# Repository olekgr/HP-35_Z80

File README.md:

# HP-35-Z80
Build HP35 scientic calculator clone with Z80 cpu from scratch.

## Intro

This DIY page is about building a HP35 clone. But without using emulators, HP microcode etc. I have always wanted to write original algorithms, created by David S. Cochran and provided by William E. Egbert in 4 editions of 1977's HP Journal, please see <a href="https://github.com/olekgr/HP-35_Z80/tree/main/arch">arch</a>.

As the original HP35 was built 50 years ago, this is a good time to do the same.

All fuctions are written with BCD arithmetic, I haven't used BCD - to binary conversion.

## Number format

For this HP35 clone, I chose a BCD floating point format. It uses an exponent byte, a sign byte and eight bytes of fractional part  (80 bits total). 

The sign byte holds 0x00 for positive numbers and 0x09 for negative, this byte also can hold other values in case of positive or negative overflow.

The exponent byte is the signed number power of 10, plus the offset 0x80. Note that exponent is not in BCD form, but binary. This greatly simplifies addition and substraction algorithms. Range is limited to 10^-99 and 10^99.

The fractional part is represented as 16 BCD digits packed two per byte, with an implied decimal point after the first digit (normalized form).

Only the first 12 digits are always displayed to the user; the last 4 digits exists to maintain precision (guard digits). All internal calculations are done with 16 digits, next the displayed result is always rounded to 12 digits.

As an examples:

1 is stored as 80_00_10_00_00_00_00_00_00_00

0.1 is stored as 7f_00_10_00_00_00_00_00_00_00

123 is stored as 82_00_12_30_00_00_00_00_00_00

pi/4 is stored  as 7f_00_78_53_98_16_33_97_44_83

## Negative numbers

Negative numbers are always stored as their 10's complement, with 0x09 at sign position. For example:

-1 is stored as 80_09_90_00_00_00_00_00_00_00

-12 is stored as 81_09_88_00_00_00_00_00_00_00

## Why Z80?

The Z80 is only four years younger than the HP35 :)

It has few instructions useful for making BCD arithmetic:

* RLD - rotate left decimal (used for shifting BCD numbers to the left)

* RRD - rotate right decimal (used for shifting BCD numbers to the right)

* DAA - decimal accumulator adjust (addition and substraction of BCD numbers)

## Speed

Calculations are fast, much faster than original HP35, we get the result immediately after pressing the key.

## Operating

I have made every effort to make this calculator work exactly like the original. Some functions were simple, others (most notably the CHS key which changes the sign of a number before or after it was entered) difficult. Either way, the calculator executes all the examples in the HP35 manual the same way. I have to say I use this calculator every day and it does a great job.

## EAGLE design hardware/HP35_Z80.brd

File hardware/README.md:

# HP-35-Z80
EAGLE PCB source files, schematic, gerbers etc.

## Hardware
The hardware is made as simple as possible. It consists of a Z80 CPU, 8K RAM, 8K ROM, input and output buffers and a simple address decoder. The main program takes about 6K, so it fits easily in 8K EEPROM. I chose 8K RAM (6264) only and because of availability, not need, I think 1-2K would be enough for stack and variables.

## Memory map
0000h-2000h ROM

8000h-A000h RAM

## BOM
* IC1 - Z80 - main CPU
* IC2 - AT28C64 - ROM
* IC3 - 6264 - RAM
* IC4 - 74HCT32 - control signals (memory read, write)
* IC5 - 74HCT154 - display multiplexer
* IC6 - 74HCT138 - address decoder (only 3 periph used)
* IC7 - 74HCT541 - keyboard input
* IC8, IC9 - 74HCT574 - digit and position for multiplexing 7-seg display
* OSC - 8MHz DIL14 - main clock

All SMT components in 1206 case (except C11 - "D" case)
* C1 - 10u 
* R1..R9 - 10k 
* C2..C10 100n
* R10..R17 - 220R (HP used inductors here for power saving :)
* DIS1..4 - common cathode 4x7 segment display (eg. SH5461AS)
* X1,X2 - USB MINI sockets (+5V power supply, for convenience left and right side)
* keys 1..35 Cherry MX switches

## Errors

None found :)

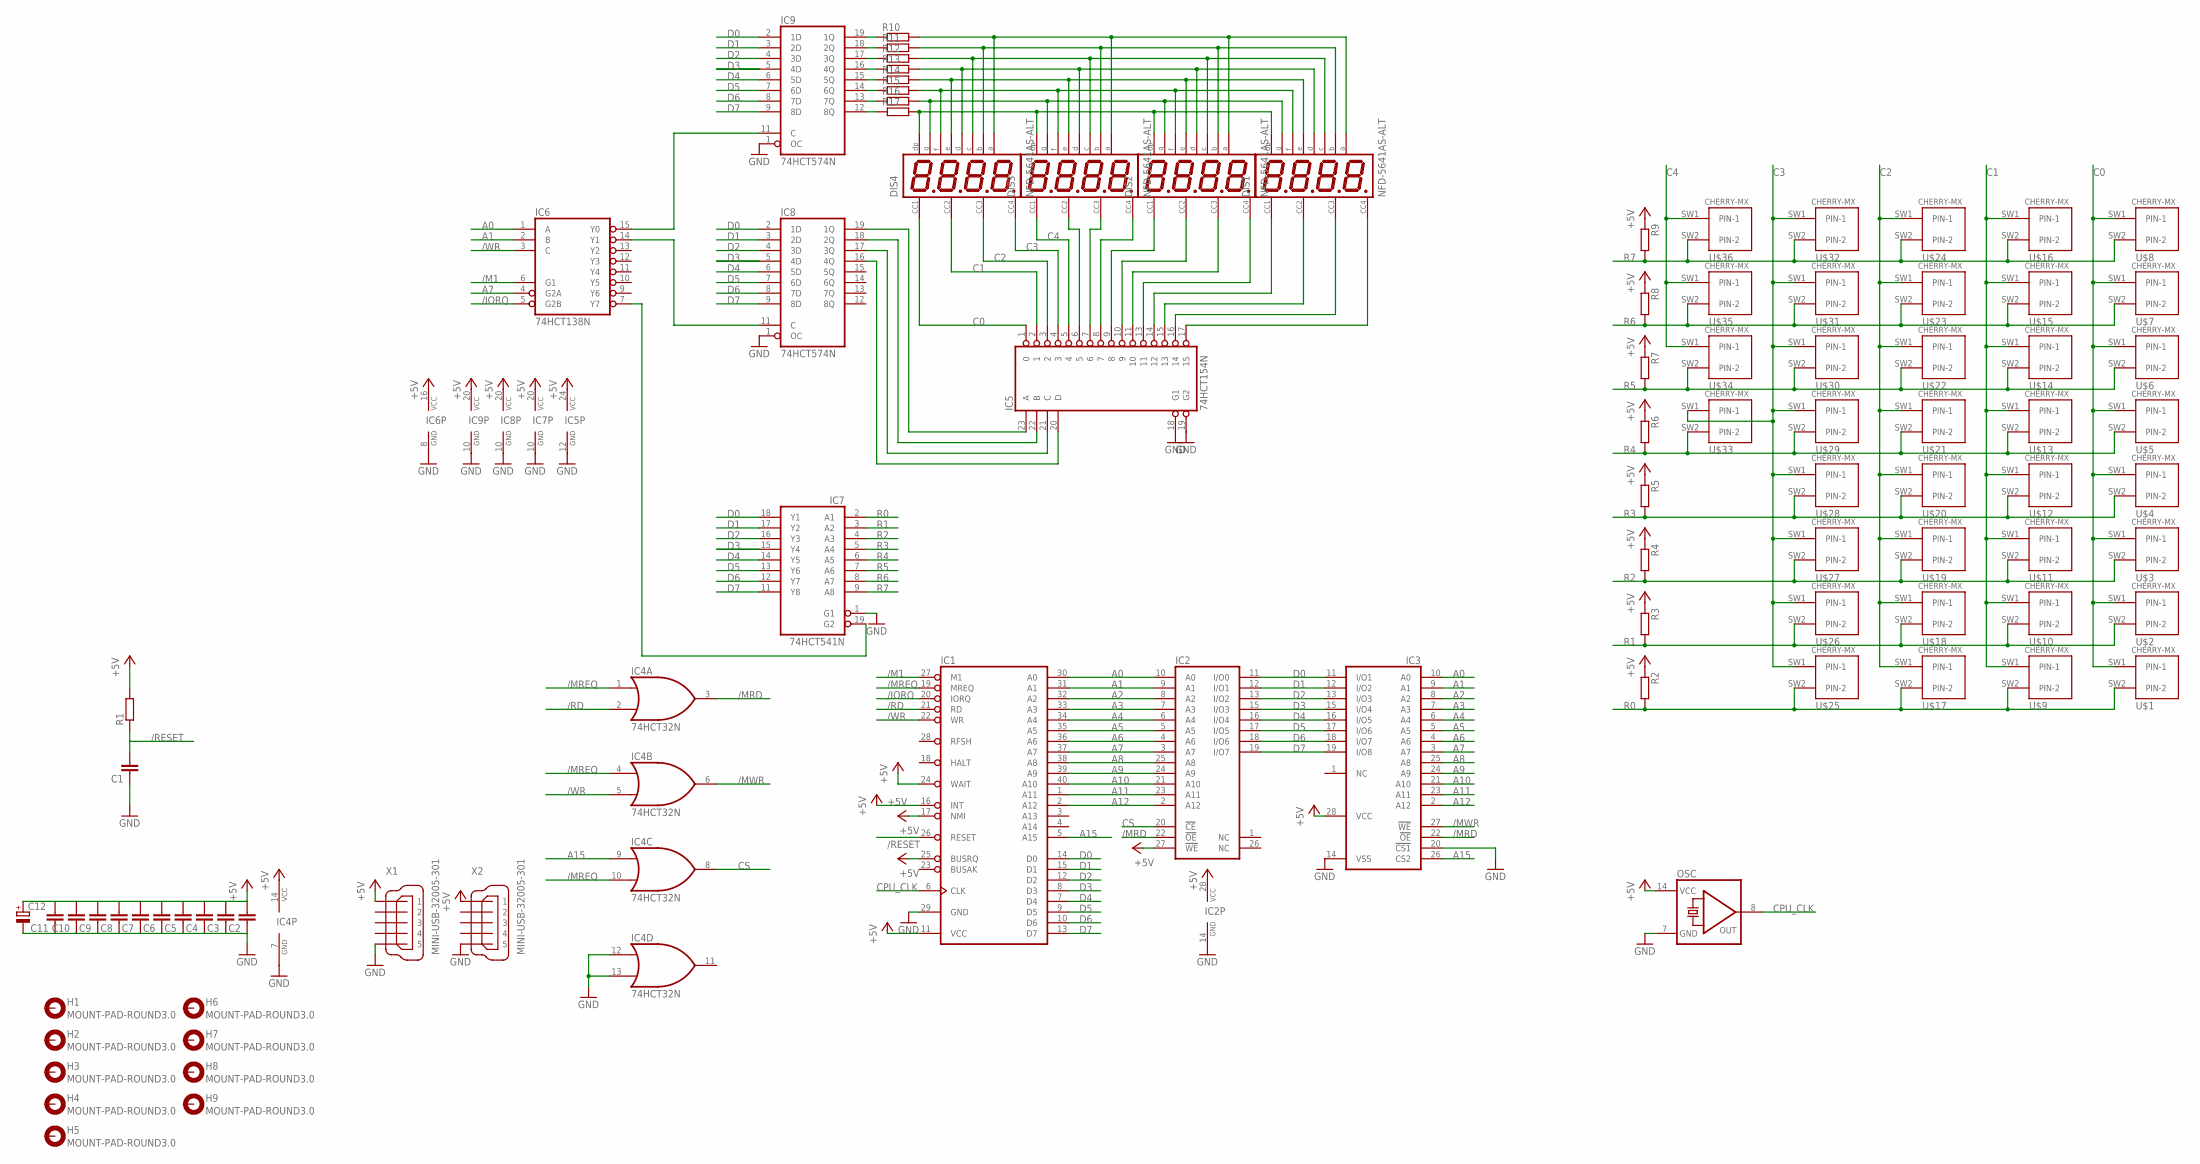
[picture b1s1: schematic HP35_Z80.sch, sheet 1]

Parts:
C1, C2, C3, C4, C5, C6, C7, C8, C9, C10, C11: C-EUC1206; C1206
C12: CPOL-EUSMCD; SMC_D
DIS1, DIS2, DIS3, DIS4: NFD-5641AS-ALT; NFD-5641
H1, H2, H3, H4, H5, H6, H7, H8, H9: MOUNT-PAD-ROUND3.0; 3,0-PAD
IC1: Z80CPU; DIL40
IC2: 78C64P; DIL28-6
IC3: 6264A; DIL28-6
IC4: 74HCT32N; DIL14
IC5: 74HCT154N; DIL24-6
IC6: 74HCT138N; DIL16
IC7: 74HCT541N; DIL20
IC8, IC9: 74HCT574N; DIL20
OSC: QG5860; DIL14S
R1, R2, R3, R4, R5, R6, R7, R8, R9, R10, R11, R12, R13, R14, R15, R16, R17: R-EU_R1206; R1206
U$1, U$2, U$3, U$4, U$5, U$6, U$7, U$8, U$9, U$10, U$11, U$12, U$13, U$14, U$15, U$16, U$17, U$18, U$19, U$20, U$21, U$22, U$23, U$24, U$25, U$26, U$27, U$28, U$29, U$30, U$31, U$32, U$33, U$34, U$35, U$36: CHERRY-MX
X1, X2: MINI-USB-32005-301; 32005-301

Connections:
+5V: C2.2, C3.2, C4.2, C5.2, C6.2, C7.2, C8.2, C9.2, C10.2, C11.2, C12.+, IC1.11 (VCC), IC1.16 (INT), IC1.17 (NMI), IC1.24 (WAIT), IC1.25 (BUSRQ), IC2.27 (!WE), IC2.28 (VCC), IC3.28 (VCC), IC4.14 (VCC), IC5.24 (VCC), IC6.16 (VCC), IC7.20 (VCC), IC8.20 (VCC), IC9.20 (VCC), OSC.14 (VCC), R1.2, R2.1, R3.1, R4.1, R5.1, R6.1, R7.1, R8.1, R9.1, X1.1, X2.1
/IORQ: IC1.20 (IORQ), IC6.5 (G2B)
/M1: IC1.27 (M1), IC6.6 (G1)
/MRD: IC2.22 (!OE), IC3.22 (!OE), IC4.3 (O)
/MREQ: IC1.19 (MREQ), IC4.1 (I0), IC4.4 (I0), IC4.10 (I1)
/MWR: IC3.27 (!WE), IC4.6 (O)
/RD: IC1.21 (RD), IC4.2 (I1)
/RESET: C1.2, IC1.26 (RESET), R1.1
/WR: IC1.22 (WR), IC4.5 (I1), IC6.3 (C)
A0: IC1.30 (A0), IC2.10 (A0), IC3.10 (A0), IC6.1 (A)
A1: IC1.31 (A1), IC2.9 (A1), IC3.9 (A1), IC6.2 (B)
A2: IC1.32 (A2), IC2.8 (A2), IC3.8 (A2)
A3: IC1.33 (A3), IC2.7 (A3), IC3.7 (A3)
A4: IC1.34 (A4), IC2.6 (A4), IC3.6 (A4)
A5: IC1.35 (A5), IC2.5 (A5), IC3.5 (A5)
A6: IC1.36 (A6), IC2.4 (A6), IC3.4 (A6)
A7: IC1.37 (A7), IC2.3 (A7), IC3.3 (A7), IC6.4 (G2A)
A8: IC1.38 (A8), IC2.25 (A8), IC3.25 (A8)
A9: IC1.39 (A9), IC2.24 (A9), IC3.24 (A9)
A10: IC1.40 (A10), IC2.21 (A10), IC3.21 (A10)
A11: IC1.1 (A11), IC2.23 (A11), IC3.23 (A11)
A12: IC1.2 (A12), IC2.2 (A12), IC3.2 (A12)
A15: IC1.5 (A15), IC3.26 (CS2), IC4.9 (I0)
C0: DIS4.P$12, IC5.1 (0), U$1.SW1 (PIN-1), U$2.SW1 (PIN-1), U$3.SW1 (PIN-1), U$4.SW1 (PIN-1), U$5.SW1 (PIN-1), U$6.SW1 (PIN-1), U$7.SW1 (PIN-1), U$8.SW1 (PIN-1)
C1: DIS4.P$9, IC5.2 (1), U$9.SW1 (PIN-1), U$10.SW1 (PIN-1), U$11.SW1 (PIN-1), U$12.SW1 (PIN-1), U$13.SW1 (PIN-1), U$14.SW1 (PIN-1), U$15.SW1 (PIN-1), U$16.SW1 (PIN-1)
C2: DIS4.P$8, IC5.3 (2), U$17.SW1 (PIN-1), U$18.SW1 (PIN-1), U$19.SW1 (PIN-1), U$20.SW1 (PIN-1), U$21.SW1 (PIN-1), U$22.SW1 (PIN-1), U$23.SW1 (PIN-1), U$24.SW1 (PIN-1)
C3: DIS4.P$6, IC5.4 (3), U$25.SW1 (PIN-1), U$26.SW1 (PIN-1), U$27.SW1 (PIN-1), U$28.SW1 (PIN-1), U$29.SW1 (PIN-1), U$30.SW1 (PIN-1), U$31.SW1 (PIN-1), U$32.SW1 (PIN-1), U$33.SW1 (PIN-1)
C4: DIS3.P$12, IC5.5 (4), U$34.SW1 (PIN-1), U$35.SW1 (PIN-1), U$36.SW1 (PIN-1)
CPU_CLK: IC1.6 (CLK), OSC.8 (OUT)
CS: IC2.20 (!CE), IC4.8 (O)
D0: IC1.14 (D0), IC2.11 (I/O0), IC3.11 (I/O1), IC7.18 (Y1), IC8.2 (1D), IC9.2 (1D)
D1: IC1.15 (D1), IC2.12 (I/O1), IC3.12 (I/O2), IC7.17 (Y2), IC8.3 (2D), IC9.3 (2D)
D2: IC1.12 (D2), IC2.13 (I/O2), IC3.13 (I/O3), IC7.16 (Y3), IC8.4 (3D), IC9.4 (3D)
D3: IC1.8 (D3), IC2.15 (I/O3), IC3.15 (I/O4), IC7.15 (Y4), IC8.5 (4D), IC9.5 (4D)
D4: IC1.7 (D4), IC2.16 (I/O4), IC3.16 (I/O5), IC7.14 (Y5), IC8.6 (5D), IC9.6 (5D)
D5: IC1.9 (D5), IC2.17 (I/O5), IC3.17 (I/O6), IC7.13 (Y6), IC8.7 (6D), IC9.7 (6D)
D6: IC1.10 (D6), IC2.18 (I/O6), IC3.18 (I/O7), IC7.12 (Y7), IC8.8 (7D), IC9.8 (7D)
D7: IC1.13 (D7), IC2.19 (I/O7), IC3.19 (I/O8), IC7.11 (Y8), IC8.9 (8D), IC9.9 (8D)
GND: C1.1, C2.1, C3.1, C4.1, C5.1, C6.1, C7.1, C8.1, C9.1, C10.1, C11.1, C12.-, IC1.29 (GND), IC2.14 (GND), IC3.14 (VSS), IC3.20 (!CS1), IC4.7 (GND), IC4.12 (I0), IC4.13 (I1), IC5.12 (GND), IC5.18 (G1), IC5.19 (G2), IC6.8 (GND), IC7.1 (G1), IC7.10 (GND), IC8.1 (OC), IC8.10 (GND), IC9.1 (OC), IC9.10 (GND), OSC.7 (GND), X1.5, X2.5
unnamed: IC6.15 (Y0), IC9.11 (C)
unnamed: IC5.20 (D), IC8.16 (4Q)
unnamed: IC6.14 (Y1), IC8.11 (C)
unnamed: IC5.21 (C), IC8.17 (3Q)
unnamed: IC5.22 (B), IC8.18 (2Q)
unnamed: IC5.23 (A), IC8.19 (1Q)
unnamed: IC6.7 (Y7), IC7.19 (G2)
unnamed: IC9.12 (8Q), R17.1
unnamed: IC9.13 (7Q), R16.1
unnamed: IC9.14 (6Q), R15.1
unnamed: IC9.15 (5Q), R14.1
unnamed: DIS3.P$9, IC5.6 (5)
unnamed: DIS3.P$8, IC5.7 (6)
unnamed: DIS3.P$6, IC5.8 (7)
unnamed: DIS2.P$12, IC5.9 (8)
unnamed: DIS2.P$9, IC5.10 (9)
unnamed: DIS2.P$8, IC5.11 (10)
unnamed: DIS2.P$6, IC5.13 (11)
unnamed: DIS1.P$12, IC5.14 (12)
unnamed: DIS1.P$9, IC5.15 (13)
unnamed: DIS1.P$8, IC5.16 (14)
unnamed: DIS1.P$6, IC5.17 (15)
unnamed: IC9.16 (4Q), R13.1
unnamed: IC9.17 (3Q), R12.1
unnamed: IC9.18 (2Q), R11.1
unnamed: IC9.19 (1Q), R10.1
unnamed: DIS1.P$11, DIS2.P$11, DIS3.P$11, DIS4.P$11, R10.2
unnamed: DIS1.P$3, DIS2.P$3, DIS3.P$3, DIS4.P$3, R17.2
unnamed: DIS1.P$5, DIS2.P$5, DIS3.P$5, DIS4.P$5, R16.2
unnamed: DIS1.P$10, DIS2.P$10, DIS3.P$10, DIS4.P$10, R15.2
unnamed: DIS1.P$1, DIS2.P$1, DIS3.P$1, DIS4.P$1, R14.2
unnamed: DIS1.P$7, DIS2.P$7, DIS3.P$7, DIS4.P$7, R11.2
unnamed: DIS1.P$4, DIS2.P$4, DIS3.P$4, DIS4.P$4, R12.2
unnamed: DIS1.P$2, DIS2.P$2, DIS3.P$2, DIS4.P$2, R13.2
R0: IC7.2 (A1), R2.2, U$1.SW2 (PIN-2), U$9.SW2 (PIN-2), U$17.SW2 (PIN-2), U$25.SW2 (PIN-2)
R1: IC7.3 (A2), R3.2, U$2.SW2 (PIN-2), U$10.SW2 (PIN-2), U$18.SW2 (PIN-2), U$26.SW2 (PIN-2)
R2: IC7.4 (A3), R4.2, U$3.SW2 (PIN-2), U$11.SW2 (PIN-2), U$19.SW2 (PIN-2), U$27.SW2 (PIN-2)
R3: IC7.5 (A4), R5.2, U$4.SW2 (PIN-2), U$12.SW2 (PIN-2), U$20.SW2 (PIN-2), U$28.SW2 (PIN-2)
R4: IC7.6 (A5), R6.2, U$5.SW2 (PIN-2), U$13.SW2 (PIN-2), U$21.SW2 (PIN-2), U$29.SW2 (PIN-2), U$33.SW2 (PIN-2)
R5: IC7.7 (A6), R7.2, U$6.SW2 (PIN-2), U$14.SW2 (PIN-2), U$22.SW2 (PIN-2), U$30.SW2 (PIN-2), U$34.SW2 (PIN-2)
R6: IC7.8 (A7), R8.2, U$7.SW2 (PIN-2), U$15.SW2 (PIN-2), U$23.SW2 (PIN-2), U$31.SW2 (PIN-2), U$35.SW2 (PIN-2)
R7: IC7.9 (A8), R9.2, U$8.SW2 (PIN-2), U$16.SW2 (PIN-2), U$24.SW2 (PIN-2), U$32.SW2 (PIN-2), U$36.SW2 (PIN-2)

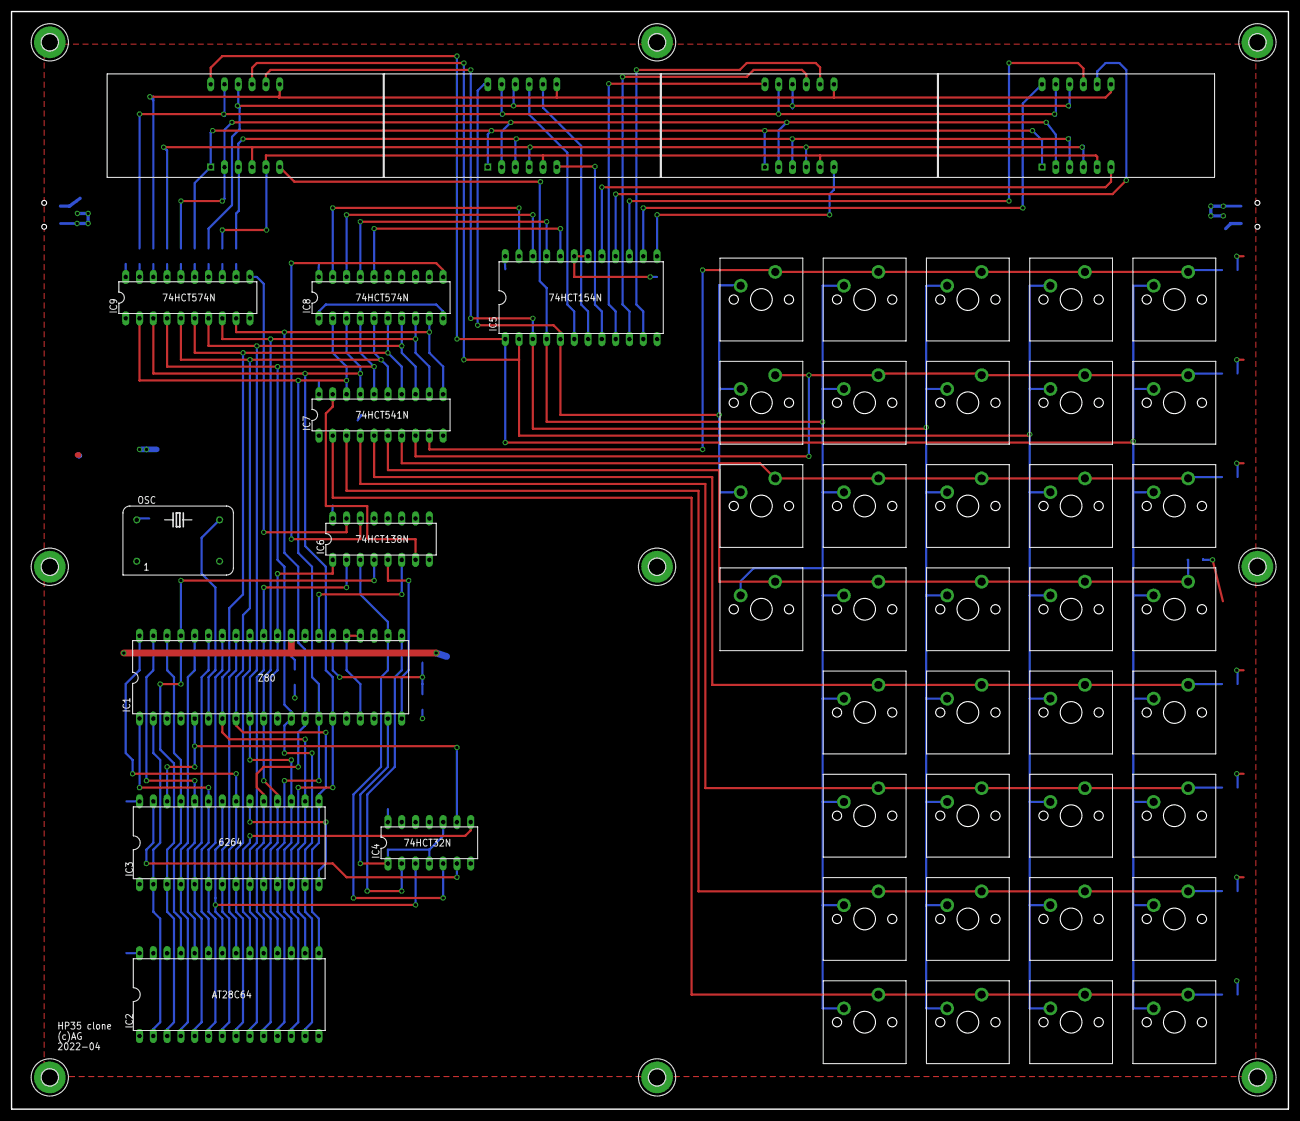
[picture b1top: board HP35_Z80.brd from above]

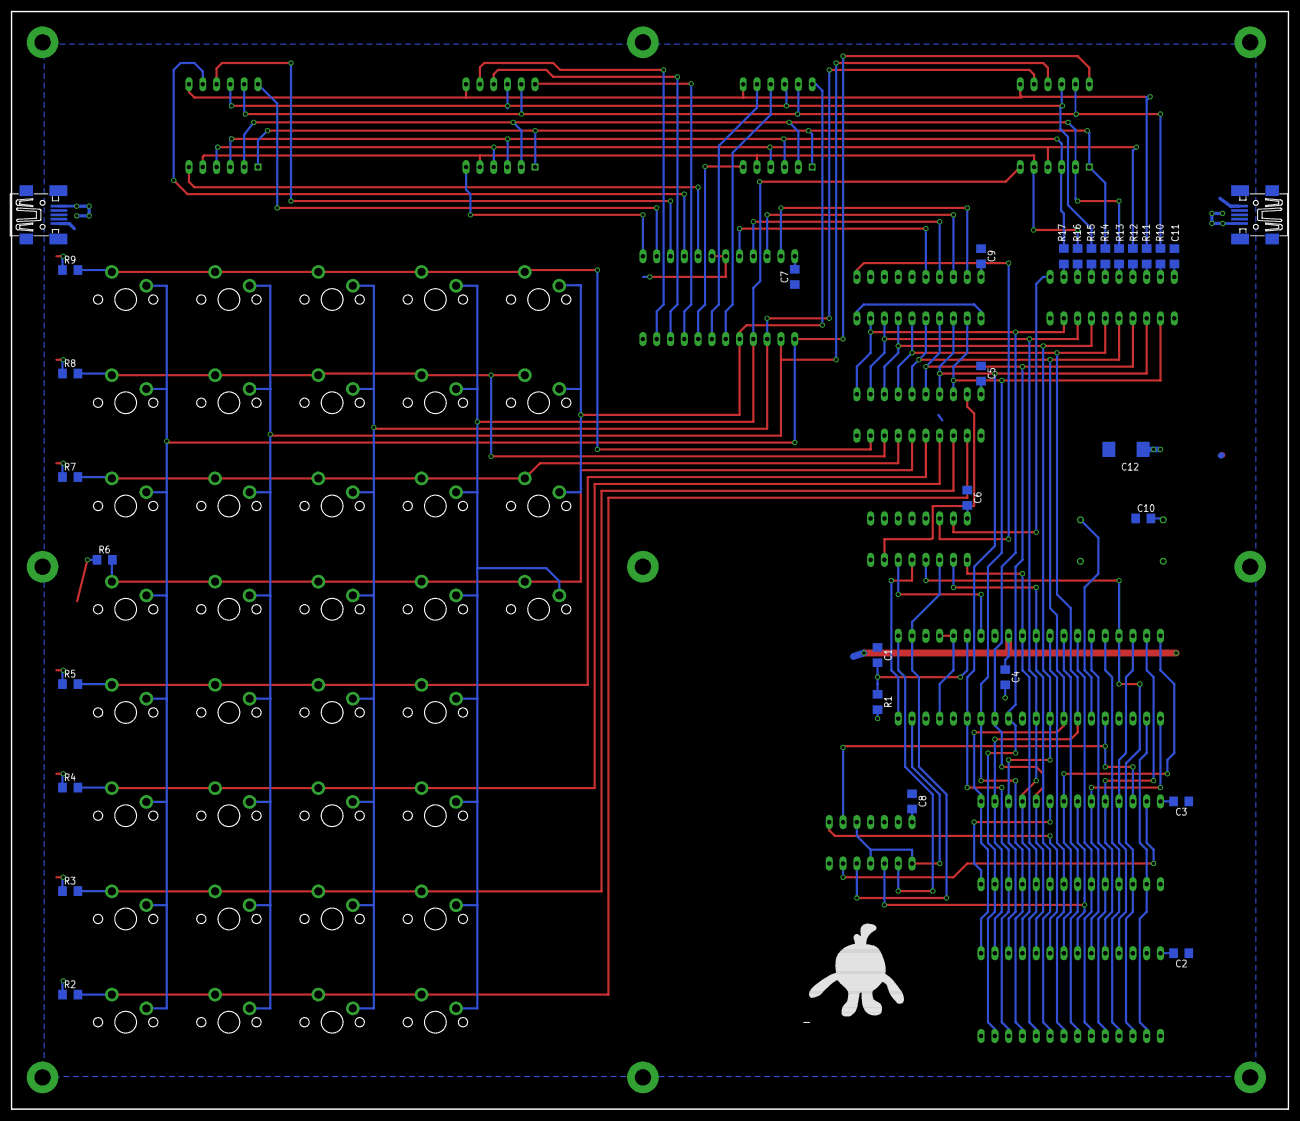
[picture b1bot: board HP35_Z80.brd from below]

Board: 2 copper layers, 235.0 x 202.0 mm, 90 parts (31 on the bottom side), 81 nets.

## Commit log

2022-04-27 add cordic papers
2022-04-27 add folders
2022-04-27 add HP papers
2022-04-27 add back label
2022-04-27 add brd
2022-04-27 add profile
2022-04-30 clean dir
2022-04-30 add firmware
2022-04-30 readme change
2022-04-30 change readme
2022-04-30 udate readme
2022-04-30 Minor linguistical changes.
2022-05-01 Meggitt.asm format
2022-05-01 link added
2022-05-01 speed info
2022-05-01 ln cleaning
2022-05-04 add pcb files
2022-05-05 fix overflow
2022-05-06 add gerbers
2022-05-07 fix fnorm
2022-05-07 minor fix
2022-05-09 final update
2022-05-10 update pcb
2022-05-12 update bom
2022-05-14 minor update
2022-05-14 update hardware
2022-05-14 error
2022-05-25 update schematic
2022-05-25 update silk
2022-05-25 update working gerbers
2022-05-28 minor display update
2022-07-09 add photo
